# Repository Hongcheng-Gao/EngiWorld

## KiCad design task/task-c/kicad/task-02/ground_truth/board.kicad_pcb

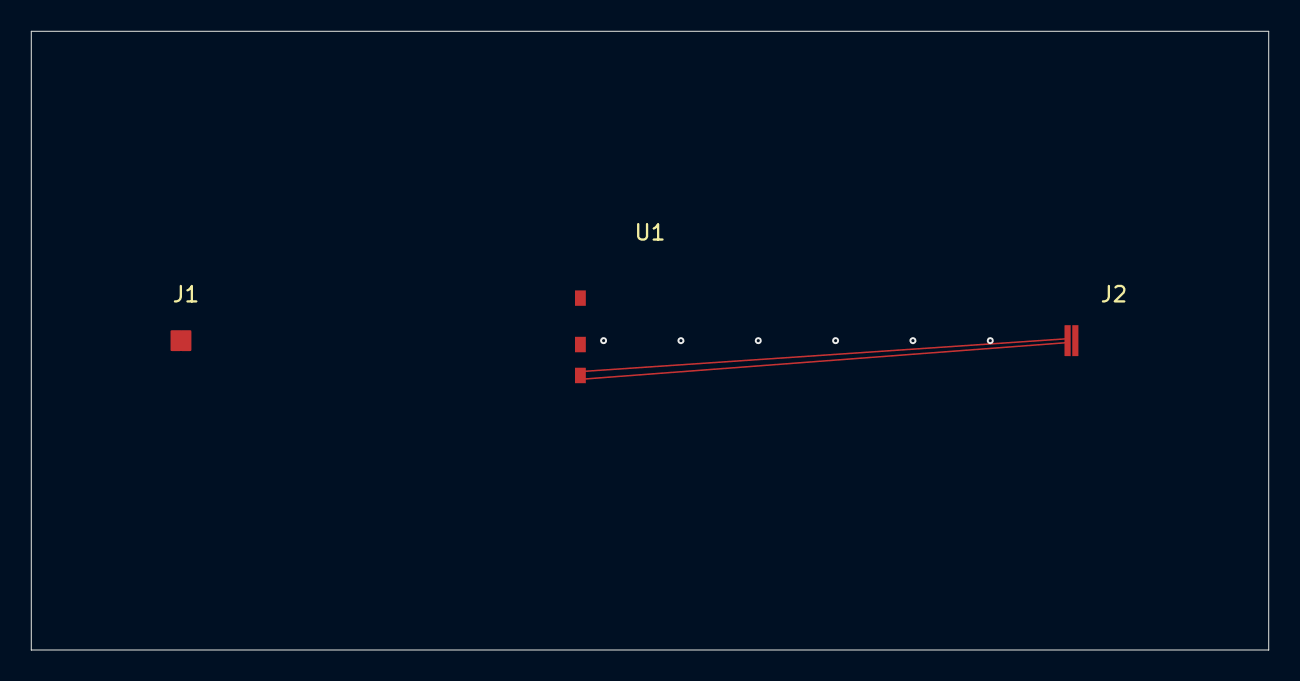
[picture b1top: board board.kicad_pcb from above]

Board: 4 copper layers, 80.0 x 40.0 mm, 3 parts (0 on the bottom side), 4 nets.

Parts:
J1: USB_MICRO; USB_B_Micro
J2: HDMI; HDMI_Molex_46765-0001
U1: MCU; LQFP-64_10x10mm_P0.5mm

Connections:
HDMI_TMDS_N: J2.2, U1.6
HDMI_TMDS_P: J2.1, U1.5
USB_DM: J1.3, U1.2
USB_DP: J1.2, U1.1

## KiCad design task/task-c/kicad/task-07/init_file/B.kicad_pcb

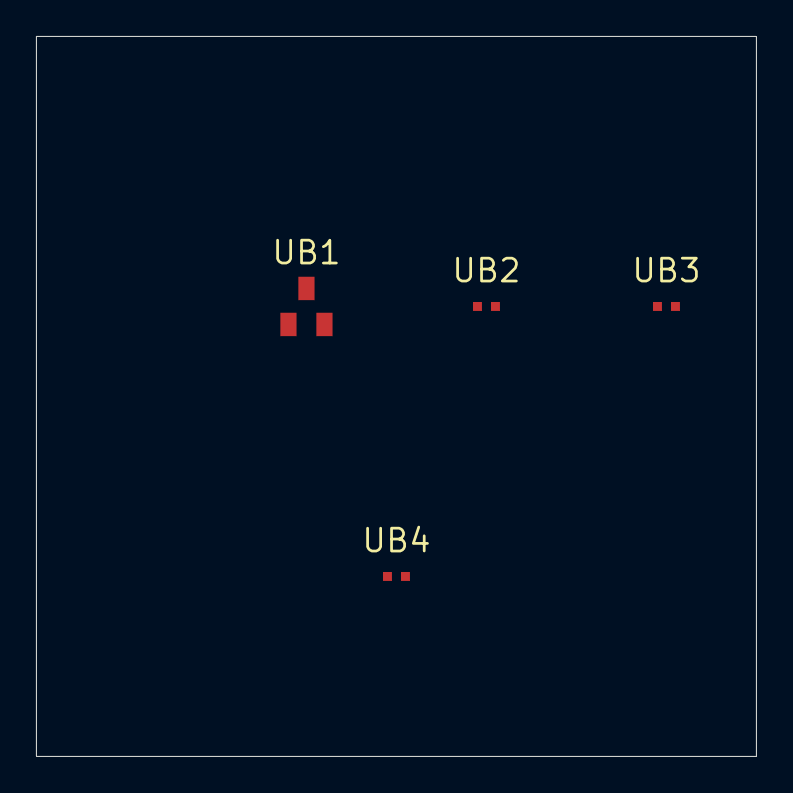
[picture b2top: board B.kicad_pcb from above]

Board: 2 copper layers, 40.0 x 40.0 mm, 4 parts (0 on the bottom side), 3 nets, no tracks yet.

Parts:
UB1: 2N3904; SOT-23
UB2: 4.7k; R_0402_1005Metric
UB3: 1k; R_0402_1005Metric
UB4: 10nF; C_0402_1005Metric

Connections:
GND: UB1.1, UB3.2, UB4.2
PWR: UB1.2, UB2.1, UB4.1
SIG: UB1.3, UB2.2, UB3.1

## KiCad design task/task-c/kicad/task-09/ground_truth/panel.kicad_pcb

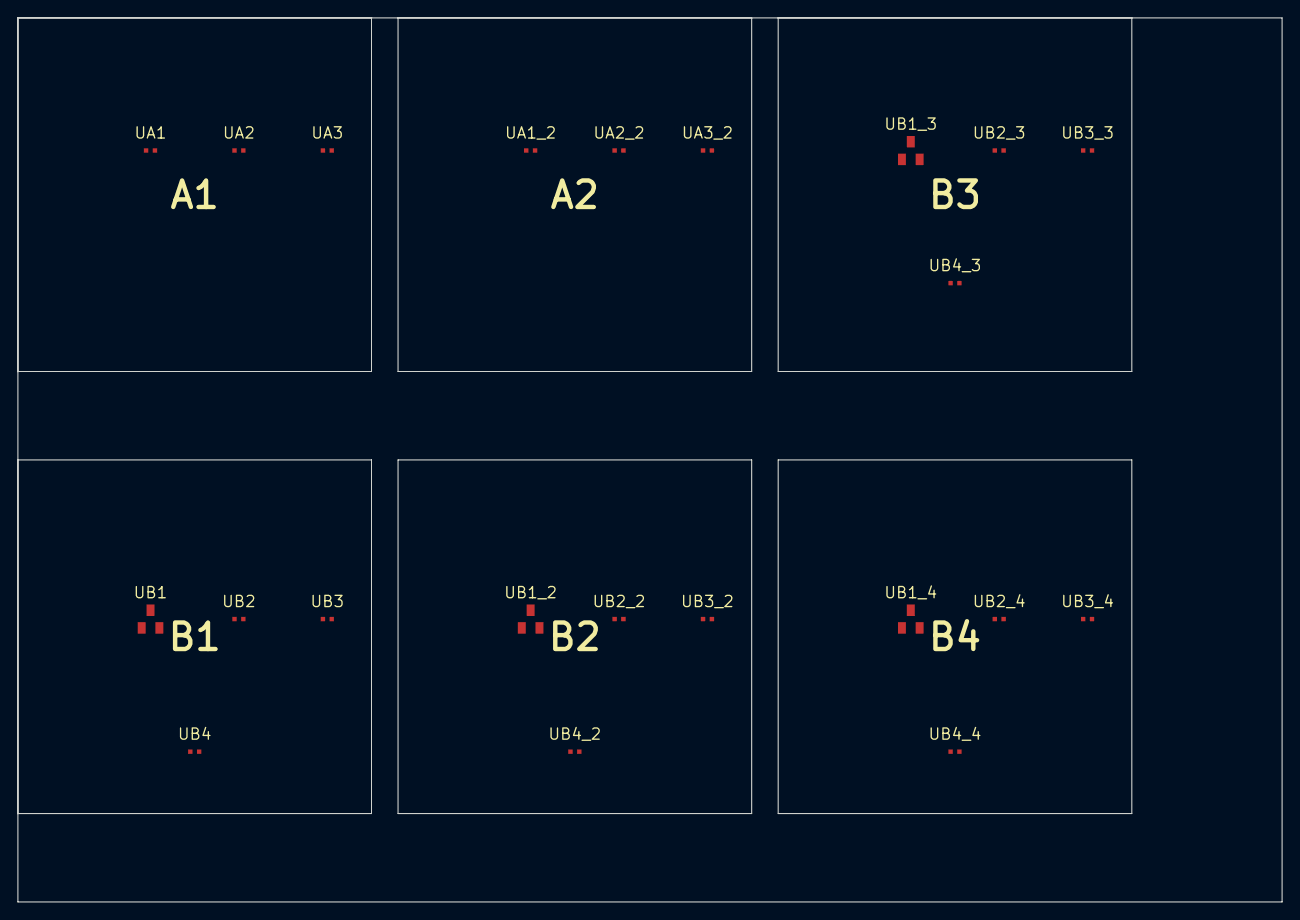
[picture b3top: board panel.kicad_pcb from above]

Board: 2 copper layers, 143.0 x 100.0 mm, 22 parts (0 on the bottom side), 4 nets, no tracks yet.

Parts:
UA1, UA1_2: 10k; R_0402_1005Metric
UA2, UA2_2: 22k; R_0402_1005Metric
UA3, UA3_2: 100nF; C_0402_1005Metric
UB1, UB1_2, UB1_3, UB1_4: 2N3904; SOT-23
UB2, UB2_2, UB2_3, UB2_4: 4.7k; R_0402_1005Metric
UB3, UB3_2, UB3_3, UB3_4: 1k; R_0402_1005Metric
UB4, UB4_2, UB4_3, UB4_4: 10nF; C_0402_1005Metric

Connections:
GND: UA1.2, UA1_2.2, UA2.2, UA2_2.2, UA3.2, UA3_2.2, UB1.1, UB1_2.1, UB1_3.1, UB1_4.1, UB3.2, UB3_2.2, UB3_3.2, UB3_4.2, UB4.2, UB4_2.2, UB4_3.2, UB4_4.2
PWR: UB1.2, UB1_2.2, UB1_3.2, UB1_4.2, UB2.1, UB2_2.1, UB2_3.1, UB2_4.1, UB4.1, UB4_2.1, UB4_3.1, UB4_4.1
SIG: UB1.3, UB1_2.3, UB1_3.3, UB1_4.3, UB2.2, UB2_2.2, UB2_3.2, UB2_4.2, UB3.1, UB3_2.1, UB3_3.1, UB3_4.1
VCC: UA1.1, UA1_2.1, UA2.1, UA2_2.1, UA3.1, UA3_2.1
